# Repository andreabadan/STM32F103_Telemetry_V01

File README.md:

# STM32F103_Telemetry_V01
Board used to log data from karting training session and send them via bluetooth.

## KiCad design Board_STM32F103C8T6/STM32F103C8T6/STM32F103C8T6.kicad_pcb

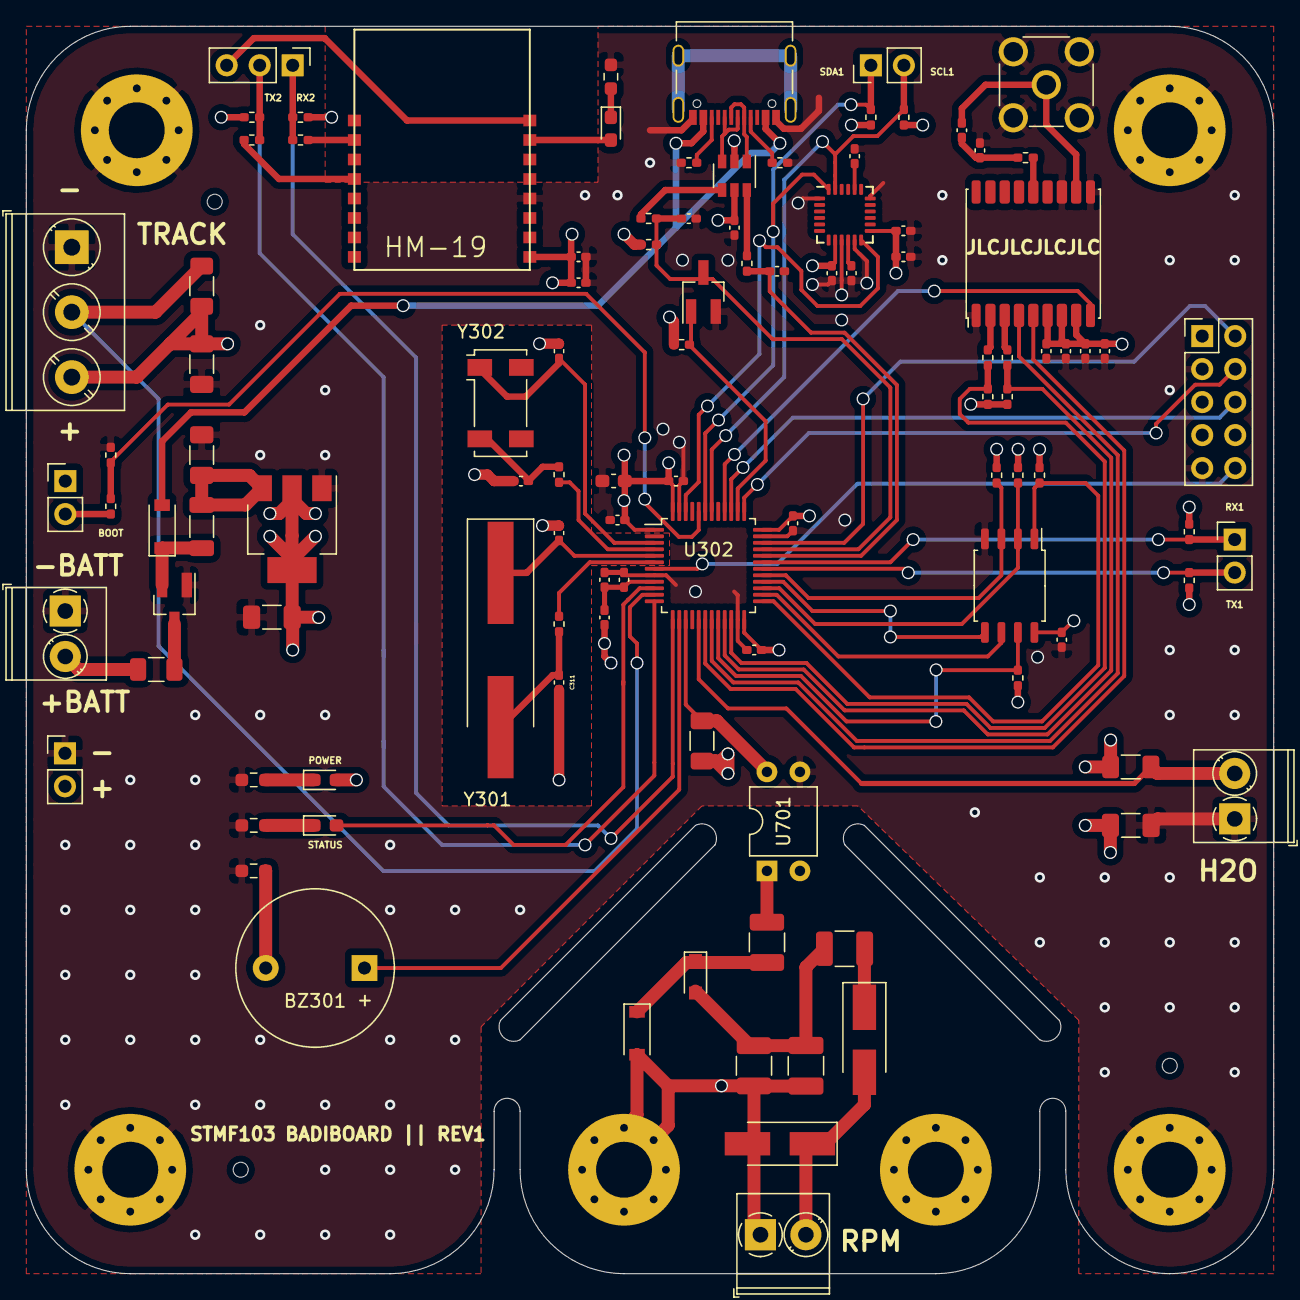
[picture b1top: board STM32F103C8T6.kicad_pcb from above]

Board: 4 copper layers, 96.0 x 96.0 mm, 115 parts (0 on the bottom side), 73 nets.

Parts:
BZ301: Buzzer; Buzzer_12x9.5RM7.6
C201: 0.1uF; C_1206_3216Metric_Pad1.33x1.80mm_HandSolder
C202, C701, C703: 10uF; C_1206_3216Metric_Pad1.33x1.80mm_HandSolder
C301: 4.7uF; C_0603_1608Metric_Pad1.08x0.95mm_HandSolder
C302, C303, C304, C305, C308, C401, C502, C503, C504, C602, C802, C803, C804: 0.1uF; C_0402_1005Metric_Pad0.74x0.62mm_HandSolder
C306: 1uF; C_0402_1005Metric_Pad0.74x0.62mm_HandSolder
C307, C805: 0.01uF; C_0402_1005Metric_Pad0.74x0.62mm_HandSolder
C309, C311: 24pF; C_0402_1005Metric_Pad0.74x0.62mm_HandSolder
C310, C312: 13pF; C_0402_1005Metric_Pad0.74x0.62mm_HandSolder
C402, C403: 47pF; C_0402_1005Metric_Pad0.74x0.62mm_HandSolder
C501, C601, C801: 10uF; C_0402_1005Metric_Pad0.74x0.62mm_HandSolder
C505: 2200pF; C_0402_1005Metric_Pad0.74x0.62mm_HandSolder
C702: 0.1uF; C_1210_3225Metric_Pad1.33x2.70mm_HandSolder
D201: B5819W; D_SOD-123
D202: GREEN; LED_0603_1608Metric_Pad1.05x0.95mm_HandSolder
D301: BLUE; LED_0603_1608Metric_Pad1.05x0.95mm_HandSolder
D601: RED; LED_0603_1608Metric_Pad1.05x0.95mm_HandSolder
D701, D702: 1N4007F; D_SMA_Handsoldering
D703: 1N4148WS; D_SOD-323_HandSoldering
D704: 5v1; D_SOD-123
F201: 500mA; Fuse_1206_3216Metric
FB201: 600 @ 600 MHz; L_1206_3216Metric_Pad1.22x1.90mm_HandSolder
H301, H302, H303, H304, H305, H306: MountingHole_Pad; MountingHole_4.3mm_M4_Pad_Via
H307, H308, H309: MountingHole; JLCPCB-Tooling-Hole
J301: BOOT; PinHeader_1x02_P2.54mm_Vertical
J401: BATTERY; TerminalBlock_Phoenix_PT-1,5-2-3.5-H_1x02_P3.50mm_Horizontal
J402: I2C; PinHeader_1x02_P2.54mm_Vertical
J403: H2O; TerminalBlock_Phoenix_PT-1,5-2-3.5-H_1x02_P3.50mm_Horizontal
J404: USB_C_Receptacle_USB2.0; USB_C_Receptacle_Palconn_UTC16-G
J405: SWD; PinHeader_2x05_P2.54mm_Vertical
J406: USART1; PinHeader_1x02_P2.54mm_Vertical
J407: CIRCUIT_SENSOR; TerminalBlock_Phoenix_PT-1,5-3-5.0-H_1x03_P5.00mm_Horizontal
J408: BLUETOOTH; PinHeader_1x03_P2.54mm_Vertical
J409: RPM; TerminalBlock_Phoenix_PT-1,5-2-3.5-H_1x02_P3.50mm_Horizontal
J410: POWER; PinHeader_1x02_P2.54mm_Vertical
J801: Conn_Coaxial; SMA_Molex_73251-2200_Horizontal
L301: 39nH; L_0402_1005Metric_Pad0.77x0.64mm_HandSolder
L801: 100nH; L_0402_1005Metric_Pad0.77x0.64mm_HandSolder
Q201: SI2301CDS-T1-BE3; SOT-23_Handsoldering
Q301: SI2312BDS-T1-BE3; SOT-23_Handsoldering
R201, R311, R603: 1.5kΩ; R_0603_1608Metric_Pad0.98x0.95mm_HandSolder
R301, R302: 2.2kΩ; R_0402_1005Metric_Pad0.72x0.64mm_HandSolder
R303, R304, R306, R308, R309, R310, R313, R314: 100kΩ; R_0402_1005Metric_Pad0.72x0.64mm_HandSolder
R305: 787Ω; R_0402_1005Metric_Pad0.72x0.64mm_HandSolder
R307: 36kΩ; R_0402_1005Metric_Pad0.72x0.64mm_HandSolder
R312: 100kΩ; R_0603_1608Metric_Pad0.98x0.95mm_HandSolder
R315, R316, R318, R320, R803: 10kΩ; R_0402_1005Metric_Pad0.72x0.64mm_HandSolder
R317: 4.7kΩ; R_0402_1005Metric_Pad0.72x0.64mm_HandSolder
R319: 1.5kΩ; R_0402_1005Metric_Pad0.72x0.64mm_HandSolder
R401, R402: 22kΩ; R_0402_1005Metric_Pad0.72x0.64mm_HandSolder
R403, R404: 5.1kΩ; R_0402_1005Metric_Pad0.72x0.64mm_HandSolder
R601, R602: 1kΩ; R_0402_1005Metric_Pad0.72x0.64mm_HandSolder
R701, R702, R706: 10kΩ; R_1206_3216Metric_Pad1.30x1.75mm_HandSolder
R703, R704: 10kΩ; R_1210_3225Metric_Pad1.30x2.65mm_HandSolder
R705: 100Ω; R_1210_3225Metric_Pad1.30x2.65mm_HandSolder
R801, R802: 0kΩ; R_0402_1005Metric_Pad0.72x0.64mm_HandSolder
U201: LD1117S33TR; SOT-223-3_TabPin2
U301: W25Q128JVS; SOIC-8_5.23x5.23mm_P1.27mm
U302: STM32F103C8T6; LQFP-48_7x7mm_P0.5mm
U401: USBLC6-2SC6; SOT-23-6
U501: MPU-6050; InvenSense_QFN-24_4x4mm_P0.5mm
U601: HM-19; HM-11_Module
U701: TLP627; DIP-4_W7.62mm
U801: MAX-M8Q; ublox_MAX
Y301: 8MHz; Crystal_SMD_HC49-SD_HandSoldering
Y302: 32.768KHz; Crystal_SMD_Abracon_ABS25-4Pin_8.0x3.8mm

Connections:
12C1_SDA: J402.1, R301.1, U302.43, U501.24
!HOLD_FLASH: R315.1, U301.7, U302.20
!WP_FLASH: R316.1, U301.3, U302.29
+3.3VA: C306.1, C307.1, L301.2, U302.9
+3V3: C202.1, C301.1, C302.1, C303.1, C304.1, C305.1, C308.1, C401.1, C501.1, C502.1, C503.1, C601.1, C602.1, C701.1, C703.1, C801.1, C802.1, C803.1, C804.1, D202.2, J301.1, J405.1, J407.3, J410.2, L301.1, R301.2, R302.2, R303.2, R304.2, R306.2, R308.2, R309.2, R310.2, R313.2, R314.2, R315.2, R316.2, R319.2, R320.1, R701.1, R702.1, R706.1, U201.2, U301.8, U302.1, U302.24, U302.36, U302.48, U401.5, U501.8, U501.13, U601.9, U801.6, U801.7, U801.8
+5V: D201.2, J404.A4, J404.A9, J404.B4, J404.B9
+BATT: F201.2, J401.2
BLUETOOTH_RESET: J408.3, U601.16
BOOT0: R317.1, R318.2, U302.44
BUZZER_STATUS: BZ301.1, U302.14
COIL_RPM: D701.1, D702.2, J409.2
GND: C201.2, C202.2, C301.2, C302.2, C303.2, C304.2, C305.2, C306.2, C307.2, C308.2, C309.2, C310.2, C311.2, C312.2, C401.2, C402.2, C403.2, C501.2, C502.2, C503.2, C504.2, C505.2, C601.2, C602.2, C701.2, C703.2, C801.2, C802.2, C803.2, C804.2, C805.2, H301.1, H302.1, H303.1, H304.1, J401.1, J403.1, J404.A1, J404.A12, J404.B1, J404.B12, J405.3, J405.5, J405.9, J407.1, J410.1, J801.2, Q201.1, Q301.2, R201.2, R311.1, R312.1, R318.1, R403.1, R404.1, R603.1, U201.1, U301.4, U302.8, U302.23, U302.35, U302.47, U401.2, U501.1, U501.9, U501.11, U501.18, U601.12, U701.3, U801.1, U801.10, U801.12
GND1: C702.2, D701.2, D704.2, H305.1, H306.1, J409.1, R704.2, U701.2
GPS_NRST: U302.40, U801.9
GPS_ONOFF: U302.18, U801.5
GPS_PPS: U302.19, U801.4
H2O_NTC+: J403.2, R702.2, U302.17
HSE_IN: C309.1, U302.5, Y301.1
HSE_OUT: R305.2, U302.6
I2C1_SCL: J402.2, R302.1, U302.42, U501.23
IMU_INTERRUPT: U302.46, U501.12
LED_STATUS: D301.2, U302.10
LSE_IN: C310.1, U302.3, Y302.1
LSE_OUT: R307.2, U302.4
NRST: J405.10, U302.7
unnamed: BZ301.2, R312.2
unnamed: C201.1, FB201.1, U201.3
unnamed: C311.1, R305.1, Y301.2
unnamed: C312.1, R307.1, Y302.2
unnamed: C504.1, U501.10
unnamed: C505.1, U501.20
unnamed: C702.1, D703.2, R703.1, R704.1
unnamed: C805.1, L801.1, R803.1
unnamed: D201.1, FB201.2, Q201.2
unnamed: D202.1, R201.1
unnamed: D301.1, R311.2
unnamed: D601.1, R603.2
unnamed: D601.2, U601.15
unnamed: D702.1, R703.2
unnamed: D703.1, D704.1, R705.2
unnamed: F201.1, Q201.3
unnamed: J301.2, R317.2
unnamed: J404.A5, R404.2
unnamed: J404.B5, R403.2
unnamed: J801.1, L801.2, U801.11
unnamed: R401.1, U401.6
unnamed: R402.2, U401.4
unnamed: R601.2, U601.2
unnamed: R602.2, U601.4
unnamed: R705.1, U701.1
unnamed: R801.2, U801.2
unnamed: R802.2, U801.3
unnamed: R803.2, U801.14
RPM_SENSOR: R706.2, U302.15, U701.4
SPI2_MISO: R313.1, U301.2, U302.27
SPI2_MOSI: U301.5, U302.28
SPI2_NSS_FLASH: R314.1, U301.1, U302.25
SPI2_SCK: U301.6, U302.26
SWCLK: J405.4, U302.37
SWDIO: J405.2, U302.34
SWO: J405.6, U302.39
TRACK_SENSOR: J407.2, R701.2, U302.11
USART1_RX: J406.1, R303.1, U302.31
USART1_TX: J406.2, R304.1, U302.30
USART2_RX: J408.1, R306.1, R601.1, U302.13
USART2_TX: J408.2, R308.1, R602.1, U302.12
USART3_RX: R310.1, R801.1, U302.22
USART3_TX: R309.1, R802.1, U302.21
USB_CONN_D+: J404.A6, J404.B6, U401.3
USB_CONN_D-: J404.A7, J404.B7, U401.1
USB_D+: C403.1, Q301.3, R319.1, R402.1, U302.33
USB_D-: C402.1, R401.2, U302.32
USB_EN: Q301.1, R320.2, U302.38

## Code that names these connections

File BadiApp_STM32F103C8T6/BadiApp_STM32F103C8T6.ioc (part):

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Mcu.Name=STM32F103C(8-B)Tx
Mcu.Package=LQFP48
Mcu.UserName=STM32F103C8Tx
PA0-WKUP.GPIOParameters=GPIO_Label
PA0-WKUP.GPIO_Label=Led status
PA0-WKUP.Signal=GPIO_Output
PA1.GPIOParameters=GPIO_Label,GPIO_ModeDefaultEXTI
PA1.GPIO_Label=Track_Sensor
PA1.GPIO_ModeDefaultEXTI=GPIO_MODE_IT_FALLING
PA1.Signal=GPXTI1
PA10.Mode=Asynchronous
PA10.Signal=USART1_RX
PA11.Mode=Device
PA11.Signal=USB_DM
PA12.Mode=Device
PA12.Signal=USB_DP
PA13.Mode=Trace_Asynchronous_SW
PA13.Signal=SYS_JTMS-SWDIO
PA14.Mode=Trace_Asynchronous_SW
PA14.Signal=SYS_JTCK-SWCLK
PA2.Mode=Asynchronous
PA2.Signal=USART2_TX
PA3.Mode=Asynchronous
PA3.Signal=USART2_RX
PA4.GPIOParameters=GPIO_Label
PA4.GPIO_Label=Buzzer
PA4.Signal=GPIO_Output
PA5.GPIOParameters=GPIO_Label,GPIO_ModeDefaultEXTI
PA5.GPIO_Label=RPM_Sensor
PA5.GPIO_ModeDefaultEXTI=GPIO_MODE_IT_FALLING
PA5.Signal=GPXTI5
PA7.GPIOParameters=GPIO_Label
PA7.GPIO_Label=H2O_NTC+
PA7.Signal=ADCx_IN7
PA8.GPIOParameters=GPIO_Speed,GPIO_Label
PA8.GPIO_Label=WP_Flash
PA8.GPIO_Speed=GPIO_SPEED_FREQ_HIGH
PA8.Signal=GPIO_Output
PA9.Mode=Asynchronous
PA9.Signal=USART1_TX
PB0.GPIOParameters=GPIO_Speed,GPIO_Label
PB0.GPIO_Label=GPS_ONOFF
PB0.GPIO_Speed=GPIO_SPEED_FREQ_LOW
PB0.Signal=GPIO_Output
PB1.GPIOParameters=GPIO_Label
PB1.GPIO_Label=GPS_PPS
PB1.Signal=GPIO_Input
PB10.Mode=Asynchronous
PB10.Signal=USART3_TX
PB11.Mode=Asynchronous
PB11.Signal=USART3_RX
PB12.Mode=NSS_Signal_Hard_Output
PB12.Signal=SPI2_NSS
PB13.Mode=Full_Duplex_Master
PB13.Signal=SPI2_SCK
PB14.Mode=Full_Duplex_Master
PB14.Signal=SPI2_MISO
PB15.Mode=Full_Duplex_Master
PB15.Signal=SPI2_MOSI
PB2.GPIOParameters=GPIO_Speed,PinState,GPIO_Label
PB2.GPIO_Label=HOLD_Flash
PB2.GPIO_Speed=GPIO_SPEED_FREQ_HIGH
PB2.PinState=GPIO_PIN_RESET
PB2.Signal=GPIO_Output
PB3.Mode=Trace_Asynchronous_SW
PB3.Signal=SYS_JTDO-TRACESWO
PB4.GPIOParameters=GPIO_Speed,GPIO_Label
PB4.GPIO_Label=GPS_NRST
PB4.GPIO_Speed=GPIO_SPEED_FREQ_LOW
PB4.Signal=GPIO_Output
PB6.GPIOParameters=GPIO_Pu
PB6.GPIO_Pu=GPIO_PULLUP
PB6.Mode=I2C
PB6.Signal=I2C1_SCL
PB7.GPIOParameters=GPIO_Pu
PB7.GPIO_Pu=GPIO_PULLUP
PB7.Mode=I2C
PB7.Signal=I2C1_SDA
PB9.GPIOParameters=GPIO_Label
PB9.GPIO_Label=IMU_Interrupt
PB9.Signal=GPIO_Input
PC13-TAMPER-RTC.GPIOParameters=GPIO_Speed,PinState,GPIO_Label
PC13-TAMPER-RTC.GPIO_Label=ToDeleate_Led
PC13-TAMPER-RTC.GPIO_Speed=GPIO_SPEED_FREQ_LOW
PC13-TAMPER-RTC.PinState=GPIO_PIN_SET
PC13-TAMPER-RTC.Signal=GPIO_Output
PC14-OSC32_IN.Mode=LSE-External-Oscillator
PC14-OSC32_IN.Signal=RCC_OSC32_IN
PC15-OSC32_OUT.Mode=LSE-External-Oscillator
PC15-OSC32_OUT.Signal=RCC_OSC32_OUT
PD0-OSC_IN.Mode=HSE-External-Oscillator
PD0-OSC_IN.Signal=RCC_OSC_IN
PD1-OSC_OUT.Mode=HSE-External-Oscillator
PD1-OSC_OUT.Signal=RCC_OSC_OUT
RCC.SYSCLKFreq_VALUE=72000000
RCC.SYSCLKSource=RCC_SYSCLKSOURCE_PLLCLK
board=custom

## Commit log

2021-08-25 First comit
    Added:
    -Bootloader
    -Application
2021-08-25 Updated application library
2021-08-29 Modified .gitignore
2021-09-04 Modified BT protocol
    Modified Bluetooth comunication protocol:
    From "Symbol" + Value to Value + "Symbol"
2021-09-25 Update GitIgnore
2021-09-25 USB DeInit function
    Added possibility to "DeInit" USB
2021-09-26 Bootloader
    Fixed issue with RAM management for bootloader function.
    Now ram address 0x20000000 to 0x200000010 are not initialized for BootLoader porpuse
2021-09-26 Added Batch files
    Added batch files to automate the Application and BootLoader writing procedure
2021-09-27 BootLoader managment
2021-09-27 Create writeAll.bat
    Create beach file to write boot and app files
2021-10-04 Bootloader MNG
2021-10-04 RTC MNG
2021-10-15 Created bootloader mng library
    Created bootloader mng library: it will manage all comunications beetwen bootloader and applicaton
2021-10-15 Added USART2
    Added possibility to upload new app from USART2
2021-10-18 Bootloader upload binary file
2021-10-19 Created BluetoothMng library
    Created BluetoothMng library to comunicate with new bluetooth 5.0 modue (HM-19)
2021-10-19 Writed function readData
2021-10-21 Creatd readData function for Bluetooth V5.0
2021-10-21 Fixed bootloader comunication with USB and UART
2021-10-21 Bluetooth v5.0 (#1)
    * Created BluetoothMng library
    Created BluetoothMng library to comunicate with new bluetooth 5.0 modue (HM-19)
    * Writed function readData
    * Creatd readData function for Bluetooth V5.0
2021-11-07 H2O temperature probe error (work in progress)
2021-12-05 Migrated project library version to 6.4.0
2021-12-05 Added possibility to read firmware version
2021-12-12 Fixed temperature reading
2021-12-12 Added Kalman Filter to temperature probe
2021-12-12 Initializate TemperatureAlarmThreeshold variable
2021-12-15 Improved filter calculation
2021-12-15 Improved filter params
2021-12-15 Added filter to RPM value calculation
2021-12-20 Added IIR Filter
2021-12-20 Changed value of initial filter
2021-12-20 Filter (#2)
    * Added Kalman Filter to temperature probe
    * Initializate TemperatureAlarmThreeshold variable
    * Improved filter calculation
    * Improved filter params
    * Added filter to RPM value calculation
    * Added IIR Filter
2021-12-20 Minor fixes
2021-12-21 Fix receipt of messages
2021-12-21 Added possibility to understand if reboot is requested from BT or USB
2021-12-21 Updated project
2021-12-21 Started to implement "Update firmware function"
    work in progress
2021-12-27 Improved bootloader communication
2021-12-28 Modified RTC settings to allow BluePill to start
    Changed source from HSE to LSE
2021-12-29 Added schematic of board
2021-12-30 Updated board design
    work in progress
2022-01-02 Improved PCB layout
2022-01-03 added files to product pcb
2022-01-03 updated layout
2022-01-08 Changed Crystals
2022-01-12 Change part number
2022-01-16 Added descriptions
2022-01-19 Added b mask layer
2022-05-08 Updated version from 5.1.9 to 6.0.5
2022-05-08 Updated version from 5.1.9 to 6.0.5 (#7)
2022-05-13 Added 3d case model
2022-05-14 Fixed 3d case model
2022-05-21 Added battery to case
2022-06-03 Changed MCU from STM32F103C8T6 to STM32F103CBT6
2022-06-03 Changed MCU from STM32F103C8T6 to STM32F103CBT6 (#9)
2022-06-03 Updated new path
2022-06-16 Modified case
    Added screws
2022-06-16 Added .bin file as build output
2022-07-10 Fix auto upload
2022-07-10 Bluetooth in bootloader comunication
2022-07-12 Fixed bluetooth update procedure
2022-07-20 Fix size to erase
2022-07-20 Fix reset currentMicrosRPMtimer (every minute)
2022-07-20 Buffer cleared before send messages
2022-08-16 Added some comments
2022-08-16 Fixed issue #11
2022-08-16 Fixed issue #11 (#12)
2022-09-16 Added possibility to simulate RPM signal
2022-09-16 Fixed RPM signal simulation
2022-09-16 Started to add NAND managment
2022-09-18 BT functions renamed
2022-09-20 Logic added to manage log writing times
2022-09-25 Changed configuration of SPI2 serial line
2022-10-31 Writed Memory Mng functions
2022-11-01 Memory mng (#13)
    * Logic added to manage log writing times
    * Changed configuration of SPI2 serial line
    * Writed Memory Mng functions
    * Writed Memory Mng functions
2022-11-01 Added .lst to project file, fixed #10
    Added compiler option: "-Wa,-adhlns="$(@:%.o=%.lst)""
2022-11-01 Updated project libraries
2023-01-26 Added schematic of board on PDF file
2023-01-31 Added RPM simulation
2023-01-31 Change simulation period
